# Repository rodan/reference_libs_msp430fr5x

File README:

reference libraries used in MSP430FR5xxx projects.

 homepage:        https://github.com/rodan/reference_libs_msp430fr5x
 author:          Petre Rodan <2b4eda@subdimension.ro>
 license:         BSD

 contains drivers for the following:

 * driverlib
  - TI MSP430 DriverLib 2.91.08.00

 * glue
  - i2c with blocking implementation based on the TI DriverLib
  - i2c controlled by interrupts (IRQ_I2C)
  - bitbanged i2c
  - uart0 (UCA0)
  - system messagebus
  - Honeywell High Accuracy Ceramic (HSC) and Standard Accuracy Ceramic (SSC) piezoresistive silicon pressure sensors
  - Sensirion SHT 1x humidity and temperature sensors
  - Maxim DS3231

 * tests
  - a Makefile driven collection of unit tests for different drivers

 * tools
  - generic script for flashing uCs

 parts of the code were originally forked from the openchronos-ng project [1]. 

 software requirements:

   msp430 toolchain

[1] http://openchronos-ng.sourceforge.net

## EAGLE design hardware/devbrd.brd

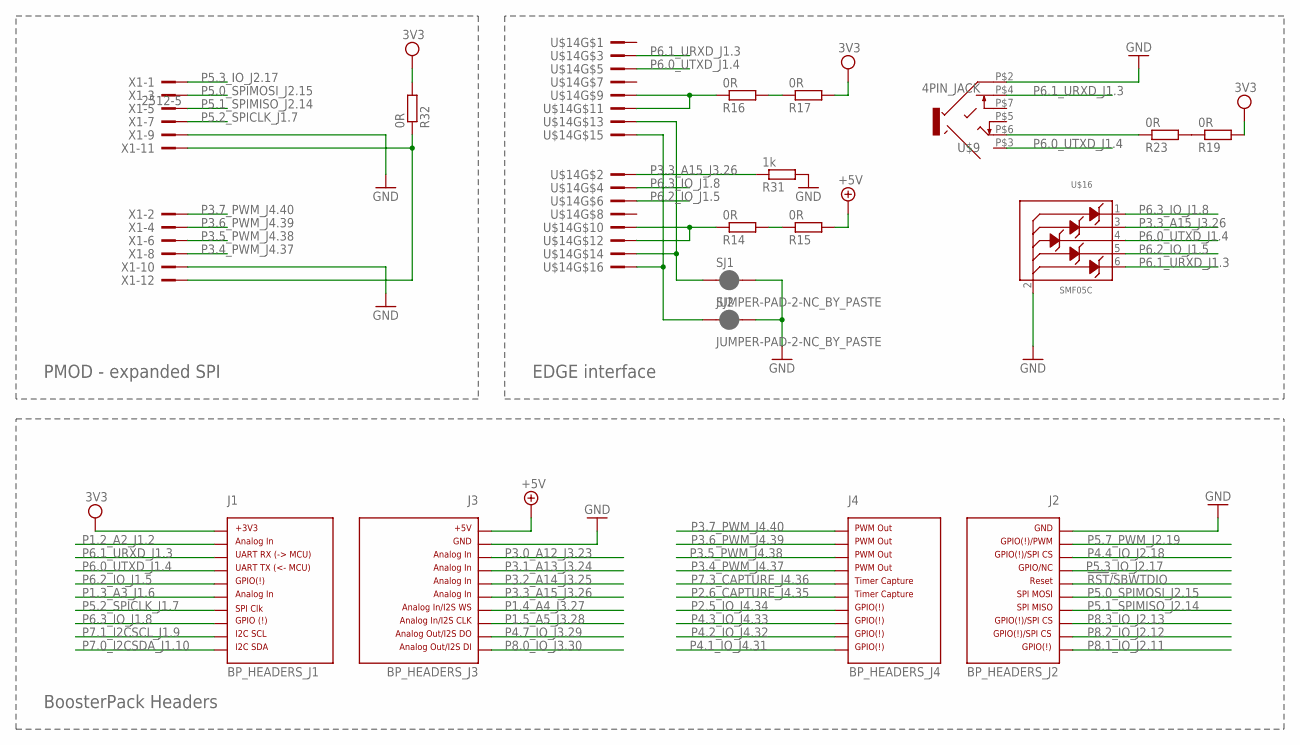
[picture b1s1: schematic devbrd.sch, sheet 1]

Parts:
J1: BP_HEADERS_J1; J1
J2: BP_HEADERS_J2; J2
J3: BP_HEADERS_J3; J3
J4: BP_HEADERS_J4; J4
R14, R16, R23: 0R; R0805W
R15, R17, R19, R32: 0R; 0204V
R31: 1k; R0805W
SJ1, SJ2: JUMPER-PAD-2-NC_BY_PASTE; PAD-JUMPER-2-NC_BY_PASTE_YES_SILK
U$9: 4PIN_JACK
U$14: 2516-; PAK100/2500-5-16
U$16: SMF05C; SC-88
X1: 2512-5; PAK100/2500-5-12

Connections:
3V3: J1.1, R17.2, R19.2, R32.2; also elsewhere on the board
!RST!/SBWTDIO: J2.16
+5V: J3.21, R15.2; also elsewhere on the board
GND: J2.20, J3.22, R31.2, SJ1.2, SJ2.2, U$9.P$2 (2), U$16.2 (ANODE), X1.9, X1.10; also elsewhere on the board
unnamed: R19.1, R23.2
unnamed: R14.2, R15.1
unnamed: R16.1, U$14.9, U$14.11
unnamed: R16.2, R17.1
unnamed: R14.1, U$14.10, U$14.12
unnamed: R23.1, U$9.P$6 (6)
unnamed: SJ1.1, U$14.13, U$14.14
unnamed: SJ2.1, U$14.15, U$14.16
unnamed: R32.1, X1.11, X1.12
P1.2_A2_J1.2: J1.2; also elsewhere on the board
P1.3_A3_J1.6: J1.6; also elsewhere on the board
P1.4_A4_J3.27: J3.27; also elsewhere on the board
P1.5_A5_J3.28: J3.28; also elsewhere on the board
P2.5_IO_J4.34: J4.34
P2.6_CAPTURE_J4.35: J4.35
P3.0_A12_J3.23: J3.23; also elsewhere on the board
P3.1_A13_J3.24: J3.24; also elsewhere on the board
P3.2_A14_J3.25: J3.25; also elsewhere on the board
P3.3_A15_J3.26: J3.26, R31.1, U$14.2, U$16.3 (CATODE2)
P3.4_PWM_J4.37: J4.37, X1.8
P3.5_PWM_J4.38: J4.38, X1.6
P3.6_PWM_J4.39: J4.39, X1.4
P3.7_PWM_J4.40: J4.40, X1.2
P4.1_IO_J4.31: J4.31
P4.2_IO_J4.32: J4.32
P4.3_IO_J4.33: J4.33
P4.4_IO_J2.18: J2.18
P4.7_IO_J3.29: J3.29; also elsewhere on the board
P5.0_SPIMOSI_J2.15: J2.15, X1.3
P5.1_SPIMISO_J2.14: J2.14, X1.5
P5.2_SPICLK_J1.7: J1.7, X1.7
P5.3_IO_J2.17: J2.17, X1.1
P5.7_PWM_J2.19: J2.19
P6.0_UTXD_J1.4: J1.4, U$9.P$3 (3), U$14.5, U$16.4 (CATODE3)
P6.1_URXD_J1.3: J1.3, U$9.P$4 (4), U$14.3, U$16.6 (CATODE5)
P6.2_IO_J1.5: J1.5, U$14.6, U$16.5 (CATODE4)
P6.3_IO_J1.8: J1.8, U$14.4, U$16.1 (CATODE1)
P7.0_I2CSDA_J1.10: J1.10; also elsewhere on the board
P7.1_I2CSCL_J1.9: J1.9; also elsewhere on the board
P7.3_CAPTURE_J4.36: J4.36
P8.0_IO_J3.30: J3.30
P8.1_IO_J2.11: J2.11
P8.2_IO_J2.12: J2.12
P8.3_IO_J2.13: J2.13

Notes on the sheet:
BoosterPack Headers
PMOD - expanded SPI
EDGE interface

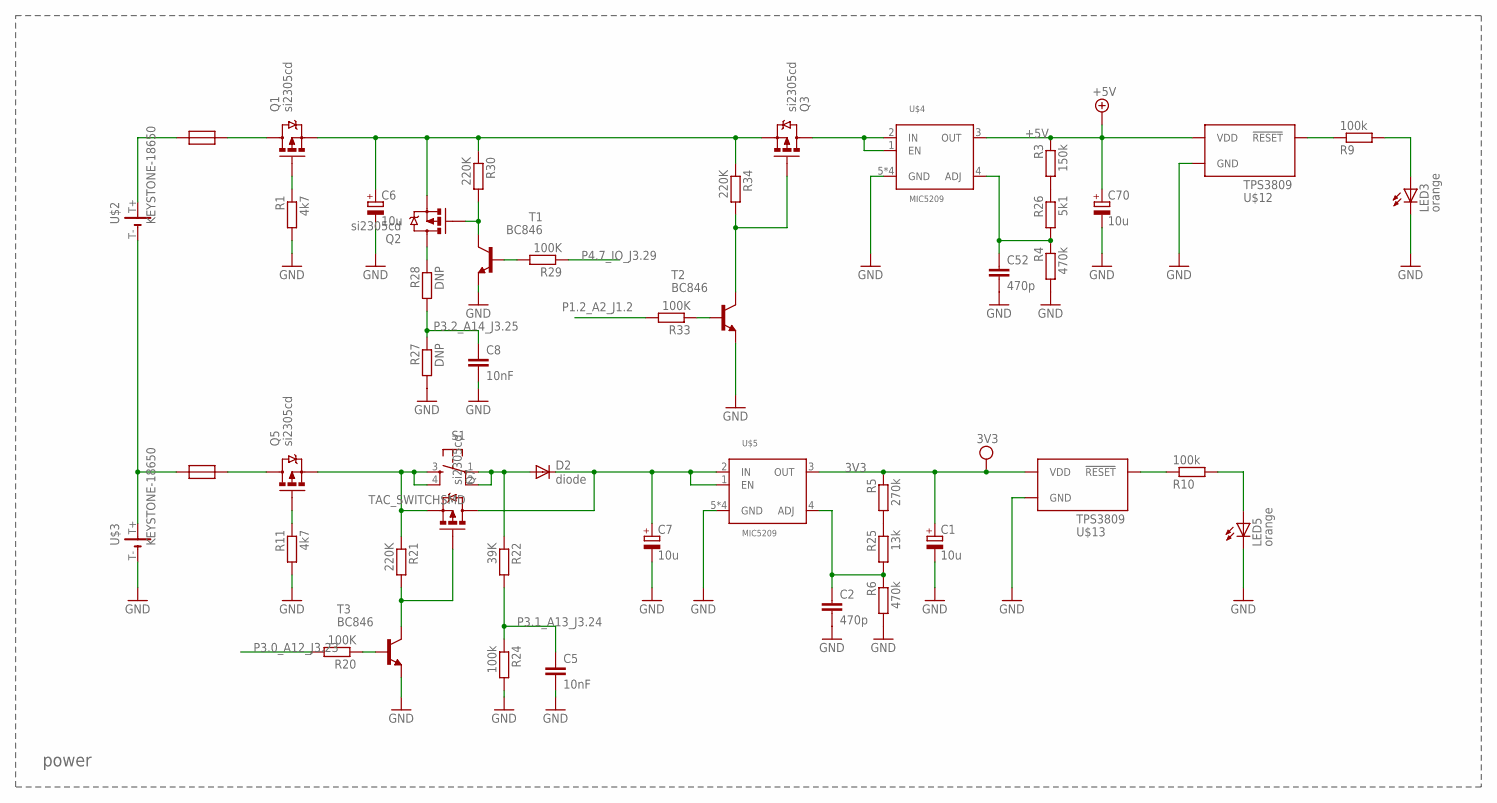
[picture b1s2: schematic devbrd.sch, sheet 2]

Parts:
C1, C6, C7, C70: 10u; 153CLV-0405
C2, C52: 470p; C0805
C5, C8: 10nF; C0805
D2: diode; SMA-DIODE
LED3, LED5: orange; CHIPLED_0805
Q1, Q2, Q3, Q5, Q7: si2305cd; SOT23-3_POWER
R1, R11: 4k7; R0805W
R3: 150k; R0805W
R4, R6: 470k; R0805W
R5: 270k; R0805W
R9, R10, R24: 100k; R0805W
R20, R29, R33: 100K; R0805W
R21, R30, R34: 220K; R0805W
R22: 39K; R0805W
R25: 13k; R0805W
R26: 5k1; R0805W
R27, R28: DNP; R0805W
S1: TAC_SWITCHSMD; TACTILE-SWITCH-SMD
T1, T2, T3: BC846; SOT23
U$2, U$3: KEYSTONE-18650; KEYSTONE_COMBO_18650
U$4, U$5: MIC5209; SO-08
U$7, U$8: RESETTABLE_0805; 0805W
U$12, U$13: TPS3809; R_PDSO_G3

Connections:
3V3: C1.+, R5.1, U$5.3 (OUT), U$13.P$3 (VDD); also elsewhere on the board
+5V: C70.+, R3.1, U$4.3 (OUT), U$12.P$3 (VDD); also elsewhere on the board
GND: C1.-, C2.2, C5.2, C6.-, C7.-, C8.2, C52.2, C70.-, LED3.C, LED5.C, R1.2, R4.2, R6.2, R11.2, R24.2, R27.2, T1.2 (E), T2.2 (E), T3.2 (E), U$3.T- (-), U$4.5 (GND), U$4.6 (GND), U$4.7 (GND), U$4.8 (GND), U$5.5 (GND), U$5.6 (GND), U$5.7 (GND), U$5.8 (GND), U$12.P$1 (GND), U$13.P$1 (GND); also elsewhere on the board
unnamed: C52.1, R4.1, R26.2, U$4.4 (ADJ)
unnamed: Q1.1 (G), R1.1
unnamed: C6.+, Q1.2 (S), Q2.2 (S), Q3.2 (S), R30.1, R34.1
unnamed: Q5.2 (S), Q7.2 (S), R21.1, S1.3, S1.4
unnamed: LED3.A, R9.2
unnamed: C2.1, R6.1, R25.2, U$5.4 (ADJ)
unnamed: Q1.3 (D), U$7.2
unnamed: Q5.3 (D), U$8.2
unnamed: R9.1, U$12.P$2 (!RESET)
unnamed: LED5.A, R10.2
unnamed: R10.1, U$13.P$2 (!RESET)
unnamed: Q7.1 (G), R21.2, T3.3 (C)
unnamed: C7.+, D2.C, Q7.3 (D), U$5.1 (EN), U$5.2 (IN)
unnamed: Q5.1 (G), R11.1
unnamed: R5.2, R25.1
unnamed: R3.2, R26.1
unnamed: Q2.3 (D), R28.1
unnamed: Q2.1 (G), R30.2, T1.3 (C)
unnamed: R20.1, T3.1 (B)
unnamed: R29.2, T1.1 (B)
unnamed: R33.1, T2.1 (B)
unnamed: Q3.3 (D), U$4.1 (EN), U$4.2 (IN)
unnamed: Q3.1 (G), R34.2, T2.3 (C)
N_BAT1: U$2.T- (-), U$3.T+ (+), U$8.1
N_BAT2: U$2.T+ (+), U$7.1
P1.2_A2_J1.2: R33.2; also elsewhere on the board
P3.0_A12_J3.23: R20.2; also elsewhere on the board
P3.1_A13_J3.24: C5.1, R22.2, R24.1; also elsewhere on the board
P3.2_A14_J3.25: C8.1, R27.1, R28.2; also elsewhere on the board
P4.7_IO_J3.29: R29.1; also elsewhere on the board
PUSH: D2.A, R22.1, S1.1, S1.2

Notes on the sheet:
power

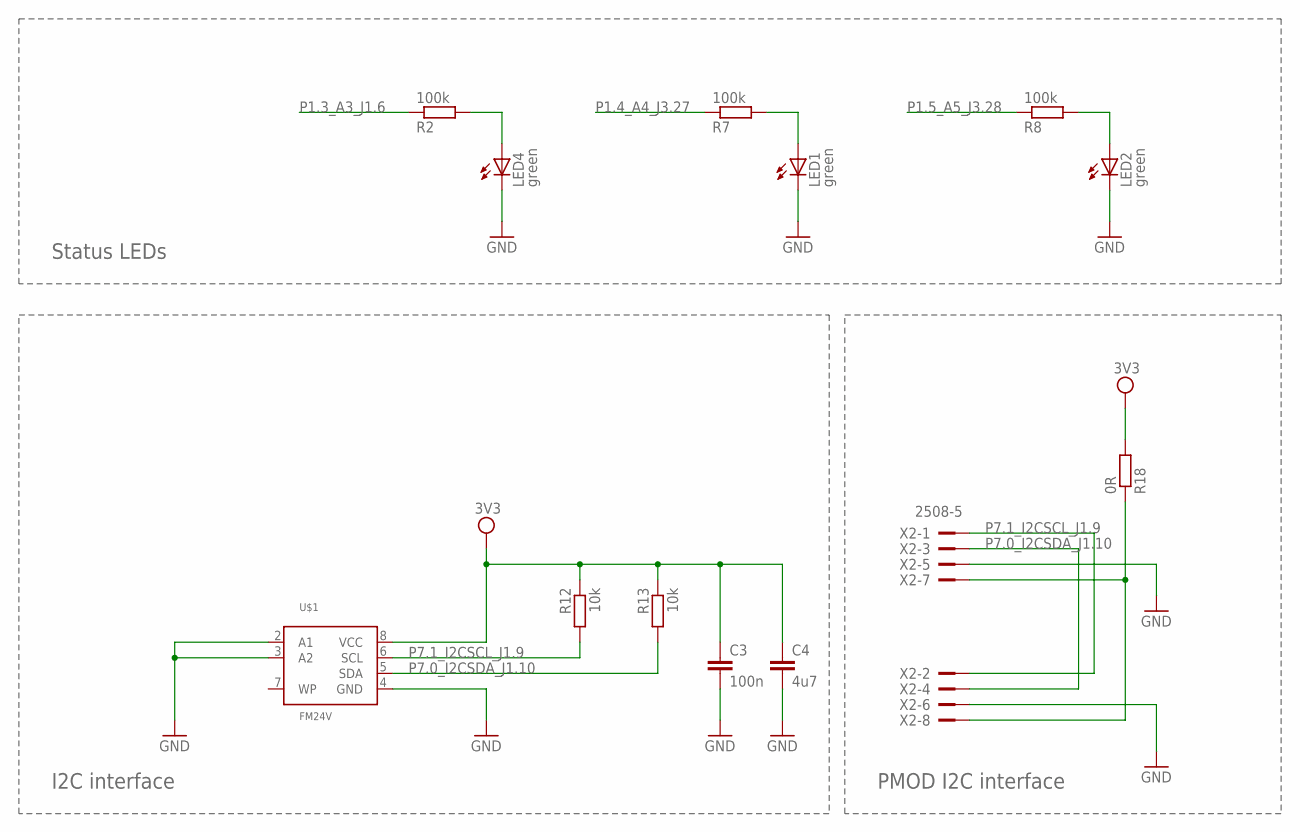
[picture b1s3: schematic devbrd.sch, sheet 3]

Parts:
C3: 100n; C0805
C4: 4u7; C0805
LED1, LED2, LED4: green; CHIPLED_0805
R2, R7, R8: 100k; R0805W
R12, R13: 10k; R0805W
R18: 0R; 0204V
U$1: FM24V; SO-08
X2: 2508-5; PAK100/2500-5-08

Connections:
3V3: C3.1, C4.1, R12.1, R13.1, R18.2, U$1.8 (VCC); also elsewhere on the board
GND: C3.2, C4.2, LED1.C, LED2.C, LED4.C, U$1.2 (A1), U$1.3 (A2), U$1.4 (GND), X2.5, X2.6; also elsewhere on the board
unnamed: LED4.A, R2.2
unnamed: LED1.A, R7.2
unnamed: LED2.A, R8.2
unnamed: R18.1, X2.7, X2.8
P1.3_A3_J1.6: R2.1; also elsewhere on the board
P1.4_A4_J3.27: R7.1; also elsewhere on the board
P1.5_A5_J3.28: R8.1; also elsewhere on the board
P7.0_I2CSDA_J1.10: R13.2, U$1.5 (SDA), X2.3, X2.4; also elsewhere on the board
P7.1_I2CSCL_J1.9: R12.2, U$1.6 (SCL), X2.1, X2.2; also elsewhere on the board

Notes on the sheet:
I2C interface
Status LEDs
PMOD I2C interface

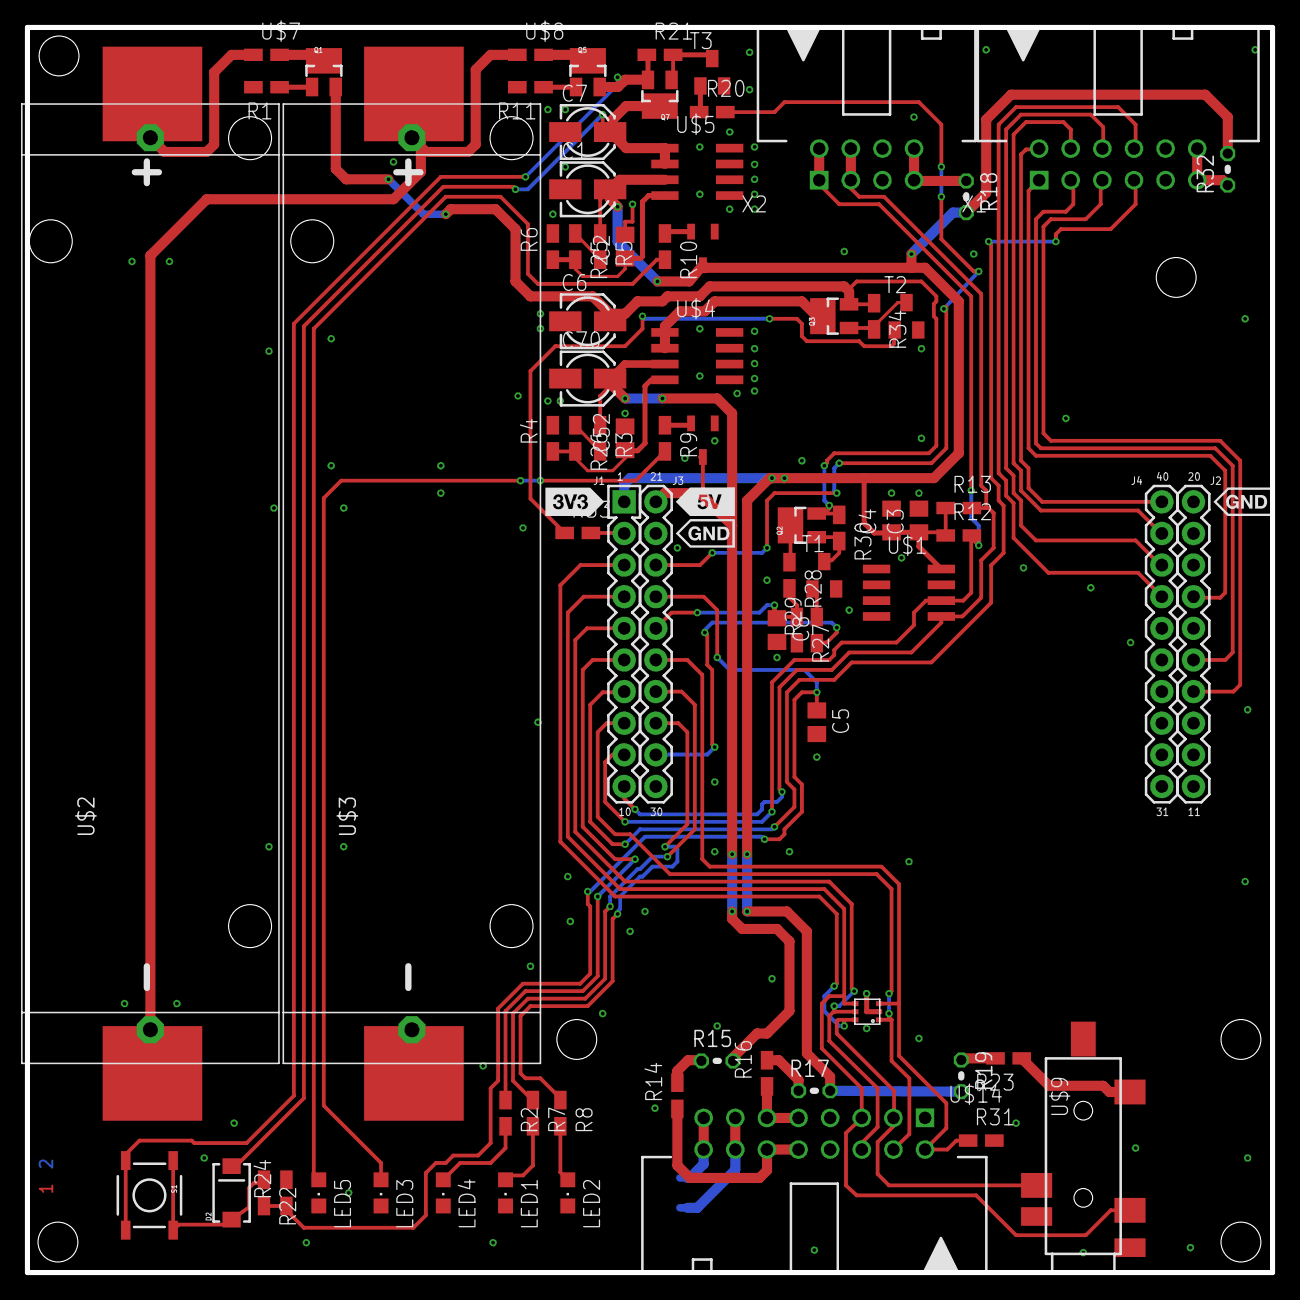
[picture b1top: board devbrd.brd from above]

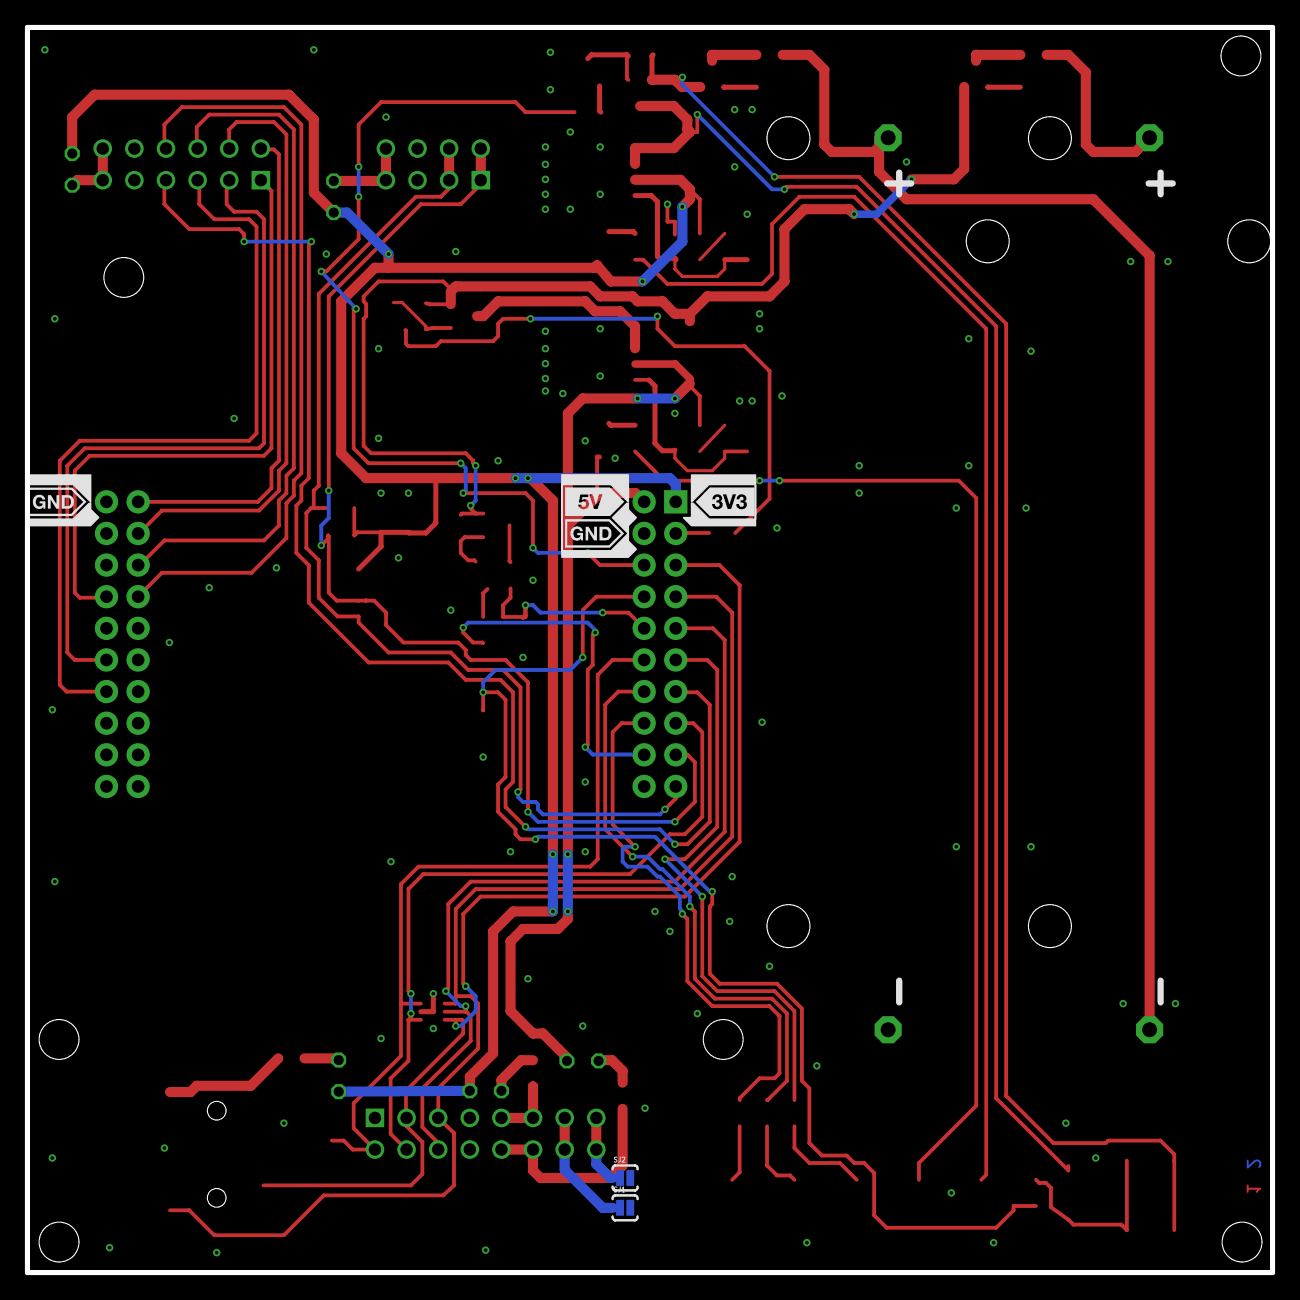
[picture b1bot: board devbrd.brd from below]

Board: 2 copper layers, 100.0 x 100.0 mm, 79 parts (2 on the bottom side), 65 nets.

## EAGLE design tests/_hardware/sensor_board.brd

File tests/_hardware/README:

hardware design files of device testing jigs

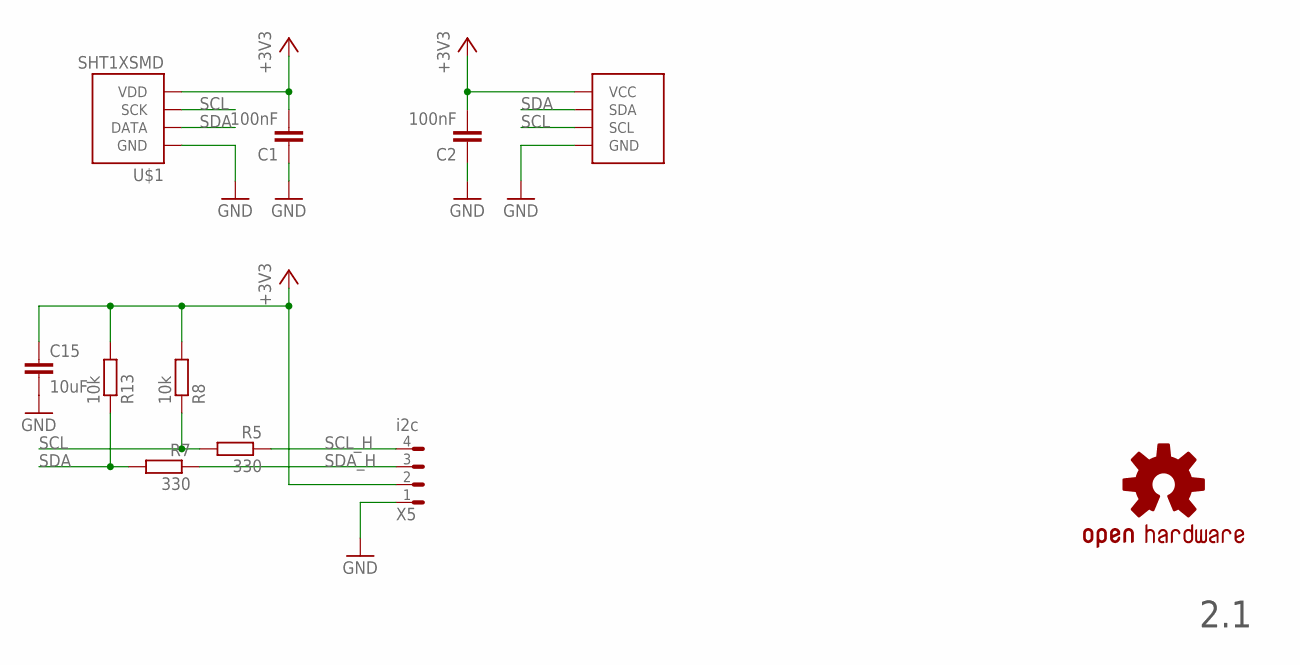
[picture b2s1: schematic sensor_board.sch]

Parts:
C1, C2: 100nF; C0805
C15: 10uF; C1206
R5, R7: 330; R0805W
R8, R13: 10k; R0805W
U$1: SHT1XSMD; SHT1X
U$2: HONEYWELL_HSC; HONEYWELL_8_SMT
U$7: OSHW-LOGOM; OSHW-LOGO-M
X5: i2c; 0530480401

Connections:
+3V3: C1.2, C2.2, C15.1, R8.2, R13.2, U$1.4 (VDD), U$2.P$2 (VCC), X5.2 (3)
GND: C1.1, C2.1, C15.2, U$1.1 (GND), U$2.P$1 (GND), X5.1 (4)
SCL: R5.2, R8.1, U$1.3 (SCK), U$2.P$4 (SCL)
SCL_H: R5.1, X5.4 (1)
SDA: R7.2, R13.1, U$1.2 (DATA), U$2.P$3 (SDA)
SDA_H: R7.1, X5.3 (2)

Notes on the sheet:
2.1

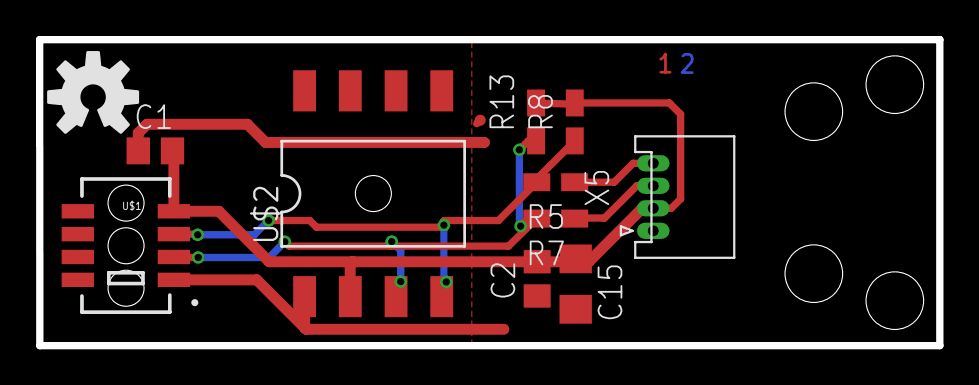
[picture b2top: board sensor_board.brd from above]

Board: 2 copper layers, 50.0 x 17.0 mm, 11 parts (0 on the bottom side), 6 nets.

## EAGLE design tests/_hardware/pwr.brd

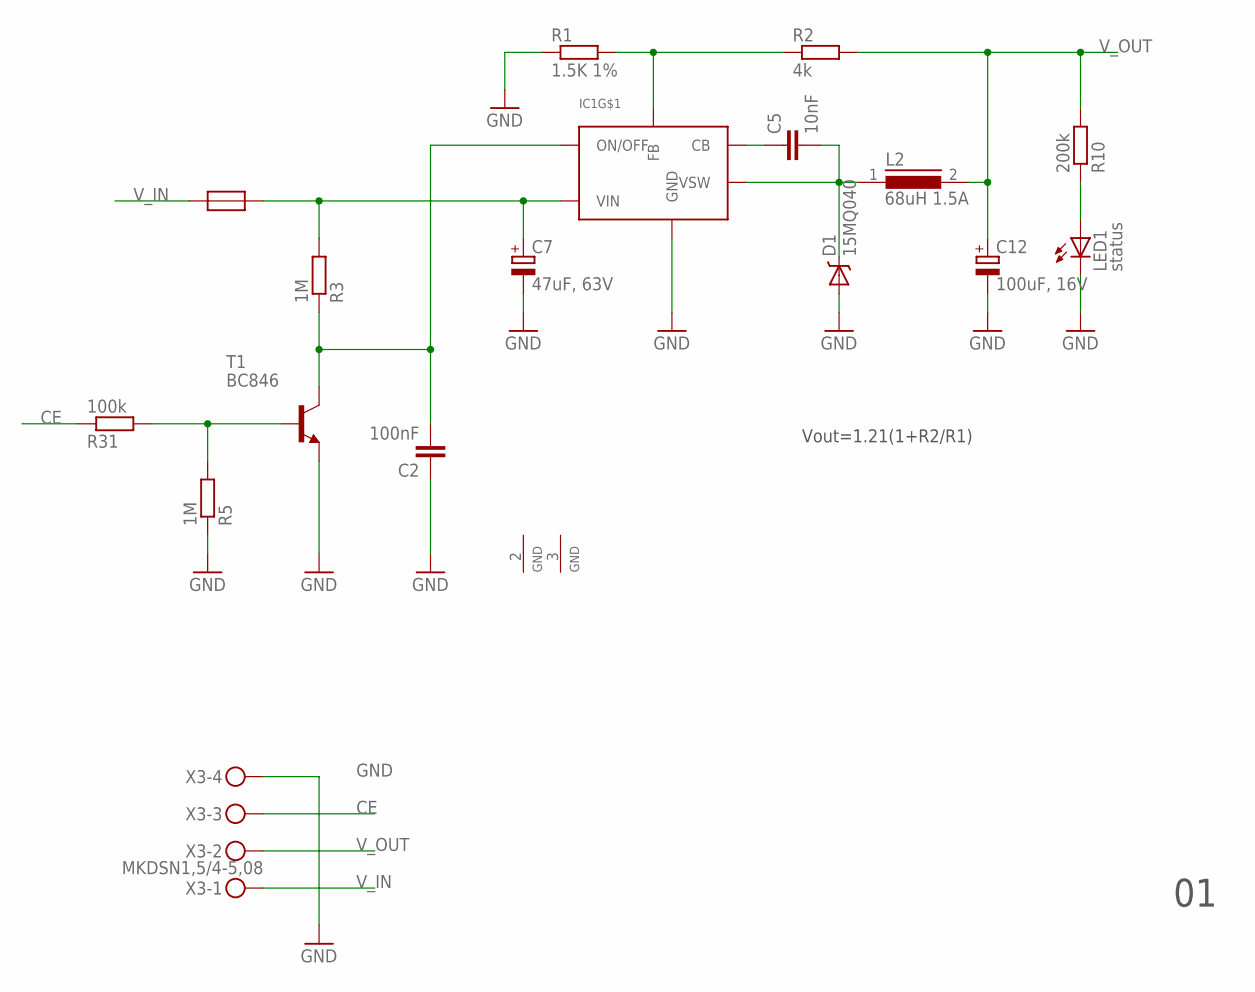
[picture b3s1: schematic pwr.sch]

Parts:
C2: 100nF; C0805
C5: 10nF; C0805
C7: 47uF, 63V; PANASONIC_F
C12: 100uF, 16V; PANASONIC_D
D1: 15MQ040; SMA-DIODE
IC1: LM2674; SO-08
L2: 68uH 1.5A; DR125
LED1: status; CHIP-LED0805
R1: 1.5K 1%; R0805W
R2: 4k; R0805W
R3, R5: 1M; R0805W
R10: 200k; R0805W
R31: 100k; R0805W
T1: BC846; SOT23
U$1: RESETTABLE_0805; 0805W
X3: MKDSN1,5/4-5,08

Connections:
CE: R31.1, X3.3
GND: C2.1, C7.-, C12.-, D1.A, IC1.2 (GND), IC1.3 (GND), IC1.6 (GND), LED1.C, R1.1, R5.1, T1.2 (E), X3.4
unnamed: LED1.A, R10.1
unnamed: C2.2, IC1.5 (ON/OFF), R3.1, T1.3 (C)
unnamed: R5.2, R31.2, T1.1 (B)
unnamed: IC1.4 (FB), R1.2, R2.1
unnamed: C5.2, D1.C, IC1.8 (VSW), L2.1
unnamed: C5.1, IC1.1 (CB)
unnamed: C7.+, IC1.7 (VIN), R3.2, U$1.2
V_IN: U$1.1, X3.1
V_OUT: C12.+, L2.2, R2.2, R10.2, X3.2

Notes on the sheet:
Vout=1.21(1+R2/R1)

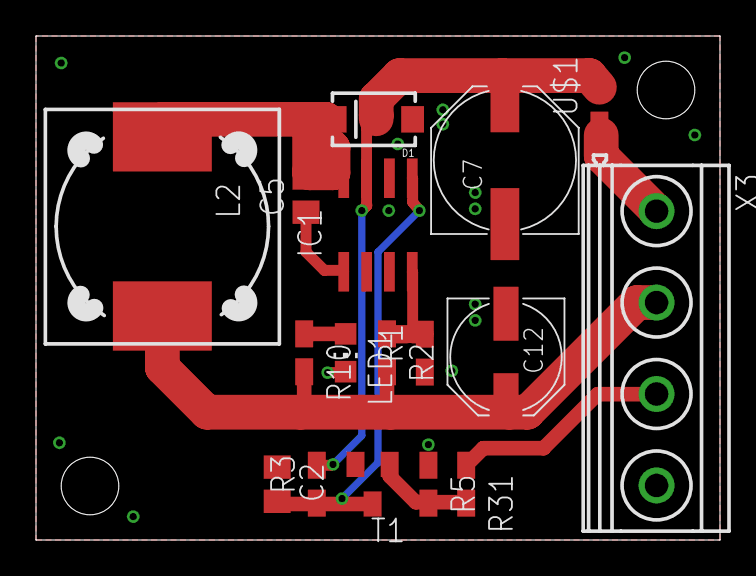
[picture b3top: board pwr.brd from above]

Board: 2 copper layers, 38.0 x 28.0 mm, 17 parts (0 on the bottom side), 11 nets.

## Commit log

2019-01-14 initial import
2019-01-14 Set theme jekyll-theme-merlot
2019-01-14 add tests
2019-01-15 bitbang working
2019-01-15 honeywell sensor working
2019-01-15 rename
2019-01-15 latest
2019-01-17 latest, non-working hardware i2c
2019-01-17 UCSWRST is on UCBxCTL1
2019-01-17 import ti libs
2019-01-20 i2c cleanup
2019-01-20 cleanup
2019-01-20 add ds3231 test
2019-01-20 sht1x example added
2019-01-22 add interrupt-driven i2c
2019-01-22 add i2c dependencies
2019-01-22 add new i2c config headers
2019-02-05 add cpp support to uart0 module
2019-02-05 add missing headers
2019-02-05 uart0 tests
2019-02-05 add different baud rates
2019-02-05 add itoa itob itoh helpers
2019-02-05 remove big table implementation for itoa
2019-02-05 8bit allignment for itoh, itob
2019-02-06 move SYS_MSG defines outside of the glue lib
2019-02-06 add USE_ITOA_LUT define
2019-02-06 add g++ unit test
2019-03-26 add standard uart baud rates for 1 and 8MHz SCLK
2019-03-30 add vishay tests
2019-07-09 testing gt911
2019-07-10 touch is working
2019-07-11 read/write config implemented
2019-07-11 callback implemented
2019-07-12 check conv version
2019-07-28 build lib objects in per-project objdir
2019-07-28 update driverlib
2019-07-29 fix dep generation
2019-08-16 add Makefile
2019-08-16 new driverlib files
2019-08-16 add support for code composer studio
2019-08-16 master Makefile cleanup
2019-08-18 ds3234 get/set clock working
2019-08-22 add support for AD7789
2019-08-22 ad7789 cleanup
2019-09-03 latest cleanup
2020-03-02 add hardware test board
2020-10-18 add cppcheck, scan-build into Makefiles
2020-10-18 cppcheck fixes
2020-10-18 add write test
2020-10-19 capacitive buttons added
2020-10-20 horizontal rescaling
2020-10-21 playing with registers
2020-10-21 hybrid config for cct screen
2020-10-22 horizontal rescaling for hybrid config
2020-12-09 testing new ccd lcd
2021-01-17 new CCT display
2021-03-07 uart ringbuffer tests
2021-04-03 switch to new clock/uart api
2021-04-03 switch to new clock/uart api 2/2
2021-05-03 new ds3234 test

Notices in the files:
parts and their libraries:
SparkFun-Electromechanical: Licensing: Creative Commons ShareAlike 4.0 International - https://creativecommons.org/licenses/by-sa/4.0
SparkFun-DiscreteSemi: Licensing: CC v3.0 Share-Alike You are welcome to use this library for commercial purposes.
